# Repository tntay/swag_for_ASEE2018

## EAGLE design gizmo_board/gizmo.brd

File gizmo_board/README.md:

# Gizmo board schematic and layout

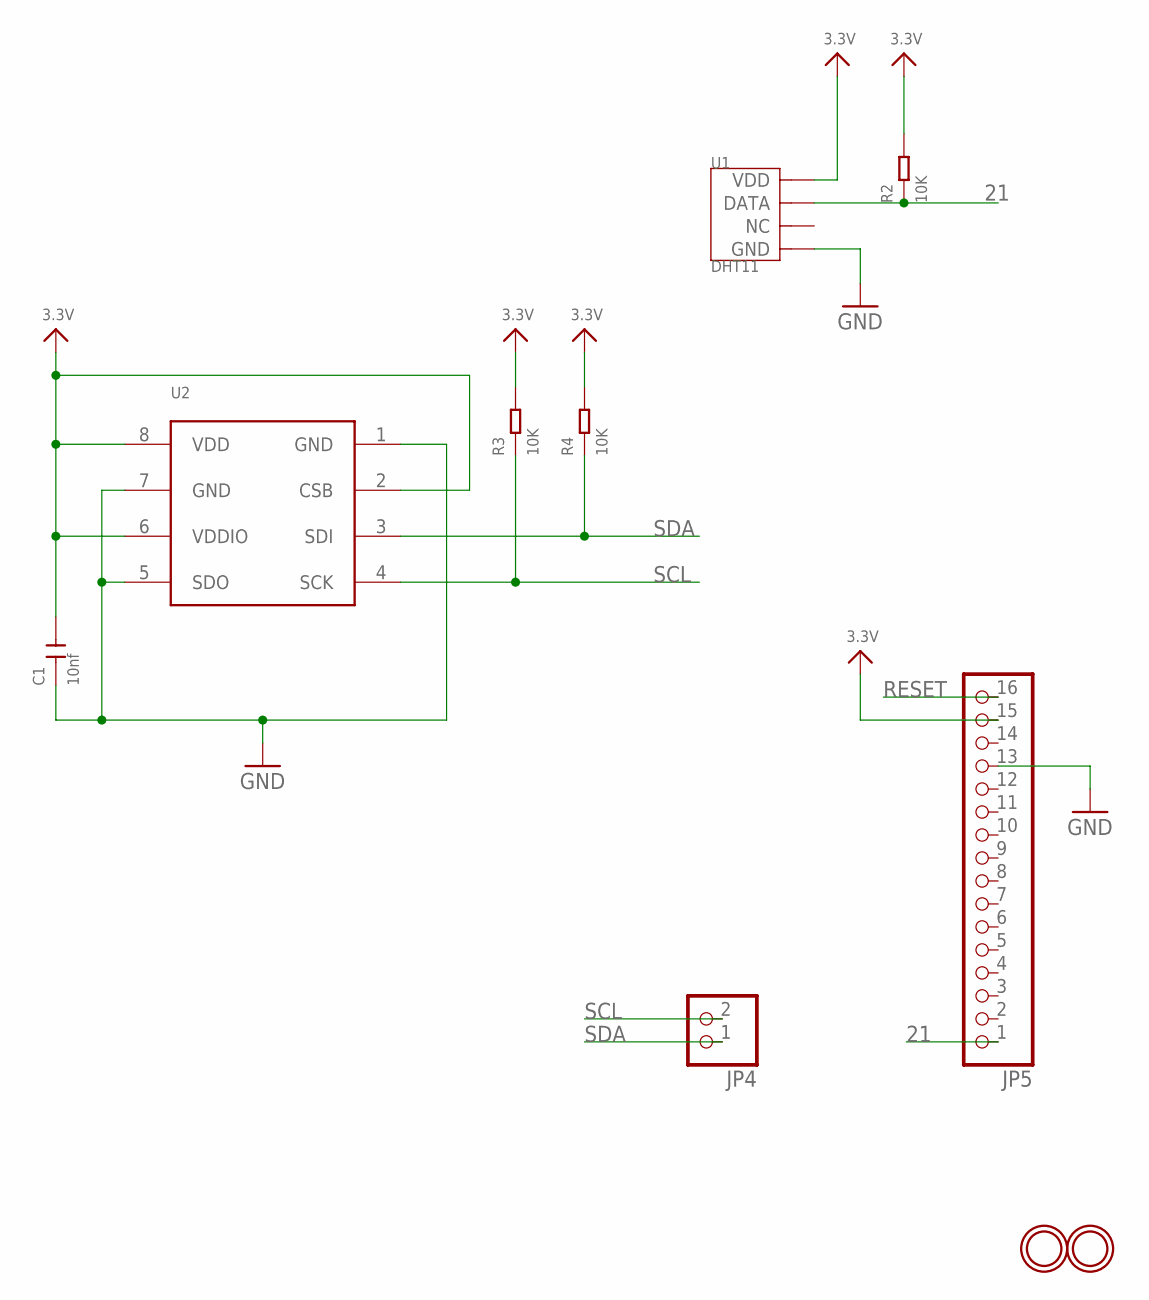
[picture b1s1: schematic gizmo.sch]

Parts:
C1: 10nf; C0805
JP4: PINHD-1X2; 1X02
JP5: PINHD-1X16; 1X16
R2, R3, R4: 10K; R0603
U1: DHT11; SNR4-2.54-15.5X12.0X5.5MM
U2: BMP280
U$31, U$32: MOUNTINGHOLE2.5; MOUNTINGHOLE_2.5_PLATED

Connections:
3.3V: C1.2, JP5.15, R2.2, R3.2, R4.2, U1.1 (VDD), U2.2 (CSB), U2.6 (VDDIO), U2.8 (VDD)
21: JP5.1, R2.1, U1.2 (DATA)
GND: C1.1, JP5.13, U1.4 (GND), U2.1 (GND), U2.5 (SDO), U2.7 (GND)
RESET: JP5.16
SCL: JP4.2, R3.1, U2.4 (SCK)
SDA: JP4.1, R4.1, U2.3 (SDI)

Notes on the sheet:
SDA
SCL
RESET

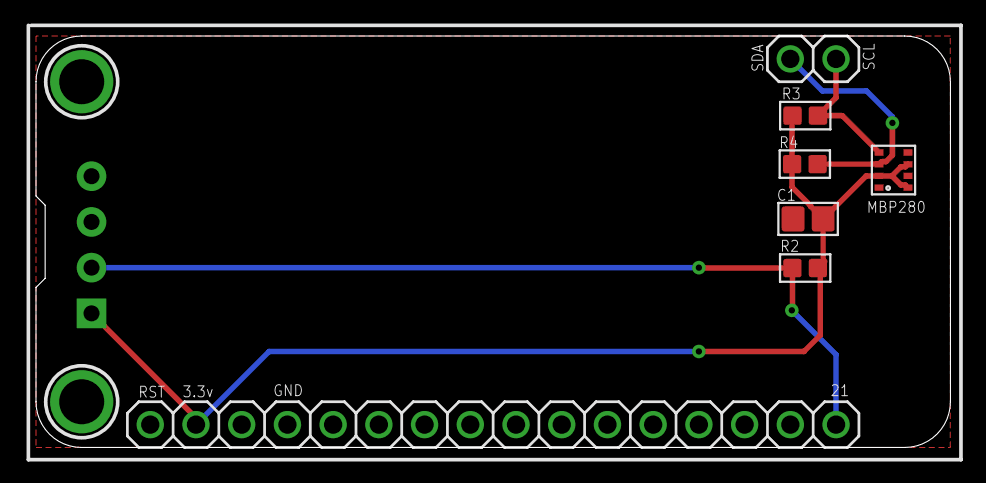
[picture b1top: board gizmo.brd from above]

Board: 2 copper layers, 50.8 x 22.9 mm, 10 parts (1 on the bottom side), 5 nets.

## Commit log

2018-10-04 add eagle files and bom for gizmo
2018-10-04 update readmes
2018-10-04 iOS app for gizmo
2018-10-04 remove pdf
2018-10-30 remove inofile
2018-10-30 add ino firmware file

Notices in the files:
parts and their libraries:
microbuilder: This work is placed in the public domain, and may be freely used for commercial and non-commercial work with the following conditions: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
